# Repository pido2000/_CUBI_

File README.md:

### Description

Simple open source bluetooth controlled wheeled robot. Mechanical design, electronics and software designs available on this repo.
Remy F. used @Gregwar's Holo as a starting point.

The initial design is a cube like robot :

https://www.youtube.com/watch?v=2ZDV0_4vD0g

https://www.youtube.com/watch?v=TOusHRbKWQg

A second design was also made to play around cart-poling:

https://www.youtube.com/watch?v=Ubej95gH9Gs

TODO:

- Add Julien's O. designs and events

- Add Julien's A. and Jérémy's designs and event (cap science)

### Simulation
Some simulation stuff (simple kinematic control, inverted pendulum tests) is available in Python here :
https://bitbucket.org/RemiFabre/cubi/src/master/simulation/

0) Installation
You'll need Python (any version should work) and pygame
```
pip install pygame
```

1) Simple control of a wheeled robot (click around)
```
python main.py
```
https://www.youtube.com/watch?v=O8ZoUAvGYmE

2) Inverted pendulum (cart-pole) simulation
```
python cart_pole.py
```
https://www.youtube.com/watch?v=xhEcLnnj7fg

### How to make it work
You'll have to install the arm cross-compilation tools. On debian-like distributions,
you can get it with:

```
    sudo aptitude install build-essential git-core dfu-util openocd python \
        python-serial binutils-arm-none-eabi gcc-arm-none-eabi libstdc++-arm-none-eabi-newlib
```
If you're running an Ubuntu 14.04 or older, you might need to install the libstdc++-arm-none-eabi-newlib packet by hand. Download link :
http://ftp.de.debian.org/debian/pool/main/libs/libstdc++-arm-none-eabi/libstdc++-arm-none-eabi-newlib_4.8.3-9+4_all.deb

Command (if a conflict rises, you can add --force-overwrite to the following line):
```
	sudo dpkg -i libstdc++-arm-none-eabi-newlib_4.8.3-9+4_all.deb
```
Go to the `firmware/src` directory and edit the `Makefile` to set the appropriate
`BOARD` variable, targetting your servo.

You can then run:

```
make
```

Use an USB cable to connect your pc with the robot's board

```
make install
```
### Bluetooth

First you need to set the name and the pasword using a cable.

```
cu -l /dev/ttyACM0
btconf <name> <pswrd>
```

Then, you can control the robot without the need of a cable. The most straight-forward way is to download the "Metabot" app from Google Play. Once on the app you can scan for devices, find your robot and pair it with your phone.

If you want to pair your PC with your robot, one method is as follows (Ubuntu).

Uninstall modemmanager (not needed but causes some issues)

```
    sudo apt-get purge modemmanager
```

Scan for bluetooth devices and save the adress (e.g. 98:D3:37:90:ED:D6) of your robot. For example, we use blueman-manager :

```
    sudo apt-get install blueman
    sudo blueman-manager
```

Assign a serial port to the connection. You can do that on the graphical interface of blueman-manager but doing it directly with rfcomm seems more robust :

```
    sudo rfcomm bind /dev/rfcomm0 98:D3:37:90:ED:D6
```

Now you can access the remote terminal on the robot with :

```
    cu -l /dev/rfcomm0
```

You might have permission access issues. Make sure you're in the dialout group or go bonkers :

```
    sudo chmod 777 /dev/rfcomm0 && cu -l /dev/rfcomm0
```

### Electronics

A board was made with all integrated components in order to drop fabrication cost. 

Top

Bottom

### Mecanics

Cubi's design is simple. It consist of a squared box. The majority was made in MDF.

Visual from Onshape

The design is transposed in the following svg file.

We also enjoyed the look of PMMA.

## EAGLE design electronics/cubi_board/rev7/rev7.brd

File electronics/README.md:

### cubi_board

Recent schematics and pcbs which integrates all the components on a standalone board in order to reduce manufacturing costs.
The board contains a µC (STM32F103CBT6), a hc-05 Bluetooth module, some voltage regulators... However, the GY-85 imu module is not integrated directly on the board.

All revisions used Eagle EDA except the last revision (rev. 8) designed on EasyEDA.

### maple-mini_board

Old schematics and pcbs using Maple Mini boards, mostly developed on Eagle EDA.

### remake_board

Recent tests made on CUBI electronic boards, developed on KiCad EDA.

The goal was to separate the motor driver and the 9V to 5V voltage regulator (the supply part) from the rest of components.
We wanted to add magnetic connectors (Pogo conn) to have a Plug And Play device.

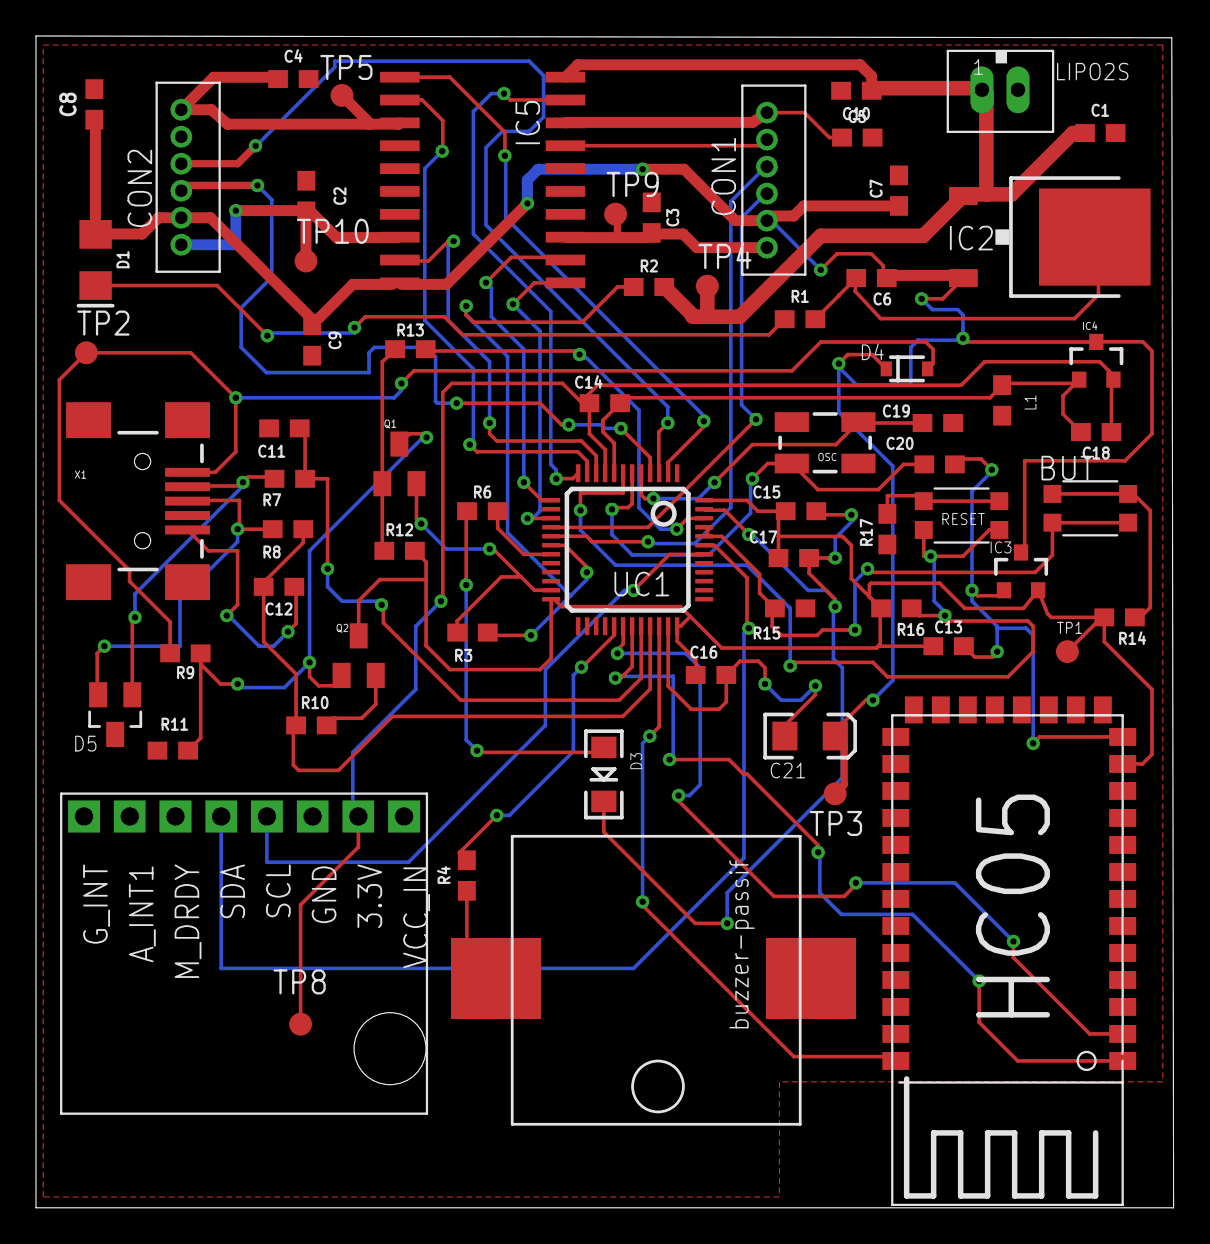
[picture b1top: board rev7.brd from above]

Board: 2 copper layers, 63.2 x 65.1 mm, 67 parts (0 on the bottom side), 47 nets.

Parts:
BUT: KMR211GLFS; PUSHBUTTON-KMR241GLFS
C1, C6: 0.1uF; 0603
C2, C3, C4, C5, C7, C8, C9, C10: 22nF; 0603
C11, C12: 47pF; 0603
C13, C18: 10uF; 0603
C14, C15, C16, C17: 1uF; 0603
C19, C20: 18pF; 0603
C21: 100uF; EIA3216
CON1, CON2: B6B-ZR
D1: FKIT-LED-1206
D3: Blue; LED-1206
D4: SOD-323
D5: PESD1CAN; SOT23
IC2: MC78M05ABDT; DPACK_3
IC3, IC4: MCP1703T-3302E/CB; SOT23
IC5: L293DD; SO20
L1: ferrite bead; 0603
LIPO2S: JST-PH_2-PIN_HEADER; JST_B2B-PH_HEADER
OSC: 8MHz; CRYSTAL-SMD-5X3
Q1, Q2: NPN-BJT; SOT23
R1: 133; 0603
R2: 60k; 0603
R3: 30k; 0603
R4: 100; 0603
R6, R13, R14, R17: 1k; 0603
R7, R8: 22; 0603
R9, R15, R16: 10k; 0603
R10: 1.5k; 0603
R11: 36k; 0603
R12: 47k; 0603
RESET: KMR211GLFS; PUSHBUTTON-KMR241GLFS
TP1, TP2, TP3, TP4, TP5, TP8, TP9, TP10: PTR1B1,27; B1,27
U$1: BUZZER-PASSIF
U$4: HC05; HC-05
U$6: GY-85
UC1: STM32F103CBT6; LQFP48
X1: USB-MINIB

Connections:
1A: IC5.2, UC1.11
2A: IC5.9, UC1.10
3/AIN: R2.1, R3.1, UC1.18
3A: IC5.12, UC1.13
4A: IC5.19, UC1.12
5V: C6.1, C7.1, C8.1, C9.1, C21.A, CON1.5, CON2.5, D1.A, D4.1, IC2.3, IC3.3, IC4.3, IC5.10, TP3.TP
9V: C1.1, C10.1, IC2.1, IC5.20, LIPO2S.P1, R2.2, TP4.TP
23_USBDP: C12.1, R8.1, R10.1, UC1.33
24_USBDM: C11.1, R7.1, UC1.32
27/PWM: R4.2, UC1.29
32: BUT.P$2, BUT.P$4, R15.2, UC1.44, UC1.45
33: R6.2, UC1.19
+5V/2: D4.2, R9.2, TP2.TP, X1.VBUS
AV+: C14.1, C18.1, IC4.2, TP8.TP, U$6.3.3, UC1.9
AV-: C14.2, C18.2, IC4.1, L1.1, UC1.8
DGND: C1.2, C2.1, C3.1, C4.2, C5.2, C7.2, C8.2, C9.2, C10.2, C11.2, C12.2, C13.2, C15.2, C16.2, C17.2, C19.2, C20.2, C21.C, CON1.2, CON2.2, D3.C, D5.3, IC3.1, IC5.4, IC5.5, IC5.6, IC5.7, IC5.14, IC5.15, IC5.16, IC5.17, L1.2, LIPO2S.P2, Q1.2, R3.2, R11.1, R15.1, R17.1, U$1.P$1, U$4.GND, U$6.GND, UC1.23, UC1.35, UC1.47, X1.GND
DISC: R13.2, UC1.46
EN: U$4.KEY, UC1.34
GNDA: C6.2, IC2.4, R1.2
MM4: CON2.3, UC1.3
MM5: CON2.4, UC1.4
MM6: CON1.4, UC1.16
MM7: CON1.3, UC1.17
MM28: IC5.1, UC1.2
MM29: IC5.11, UC1.15
unnamed: D1.C, R1.1
unnamed: R4.1, U$1.P$2
unnamed: BUT.P$1, BUT.P$3, R14.1
unnamed: R17.2, RESET.P$1, RESET.P$3
unnamed: D3.A, R6.1
unnamed: Q2.2, R10.2
unnamed: D5.1, R7.2, X1.D-
unnamed: D5.2, R8.2, X1.D+
unnamed: Q1.3, Q2.1, R9.1, R11.2
unnamed: Q1.1, R12.1, R13.1
OSC_IN: C19.1, OSC.3, UC1.5
OSC_OUT: C20.1, OSC.1, UC1.6
OUT1: C4.1, CON2.1, IC5.3, TP5.TP
OUT2: C2.2, CON2.6, IC5.8, TP10.TP
OUT3: C3.2, CON1.6, IC5.13, TP9.TP
OUT4: C5.1, CON1.1, IC5.18
RESET: R16.1, RESET.P$2, RESET.P$4, UC1.7
RX: U$4.RX, UC1.30
SCL: U$6.SCL, UC1.42
SDA: U$6.SDA, UC1.43
TX: U$4.TX, UC1.31
VCC: C13.1, C15.1, C16.1, C17.1, IC3.2, Q2.3, R12.2, R14.2, R16.2, TP1.TP, U$4.3.3, UC1.24, UC1.36, UC1.48

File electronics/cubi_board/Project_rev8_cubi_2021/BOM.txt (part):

Partlist exported from C:/Users/elkat/Documents/EAGLE/projects/electronics/rev7/rev7.sch at 24/09/2019 17:15

Part   Value               Device                     Package               Description                               FARNELL      MF MPN OC_FARNELL PROD_ID   TP_SIGNAL_NAME VALUE
BUT    KMR211GLFS          BUTTON-KMR241GLFS          PUSHBUTTON-KMR241GLFS                                                                                                        
C1     0.1uF               0.1UF-0603-25V-(+80/-20%)  0603                  0.1µF ceramic capacitors                                                 CAP-00810                0.1uF
C2     22nF                22NF/22,000PF-0603-50V-10% 0603                  0.022uF/22nF/22,000pF ceramic capacitors                                 CAP-07885                22nF 
C3     22nF                22NF/22,000PF-0603-50V-10% 0603                  0.022uF/22nF/22,000pF ceramic capacitors                                 CAP-07885                22nF 
C4     22nF                22NF/22,000PF-0603-50V-10% 0603                  0.022uF/22nF/22,000pF ceramic capacitors                                 CAP-07885                22nF 
C5     22nF                22NF/22,000PF-0603-50V-10% 0603                  0.022uF/22nF/22,000pF ceramic capacitors                                 CAP-07885                22nF 
C6     0.1uF               0.1UF-0603-25V-(+80/-20%)  0603                  0.1µF ceramic capacitors                                                 CAP-00810                0.1uF
C7     22nF                22NF/22,000PF-0603-50V-10% 0603                  0.022uF/22nF/22,000pF ceramic capacitors                                 CAP-07885                22nF 
C8     22nF                22NF/22,000PF-0603-50V-10% 0603                  0.022uF/22nF/22,000pF ceramic capacitors                                 CAP-07885                22nF 
C9     22nF                22NF/22,000PF-0603-50V-10% 0603                  0.022uF/22nF/22,000pF ceramic capacitors                                 CAP-07885                22nF 
C10    22nF                22NF/22,000PF-0603-50V-10% 0603                  0.022uF/22nF/22,000pF ceramic capacitors                                 CAP-07885                22nF 
C11    47pF                0.1UF-0603-25V-(+80/-20%)  0603                  0.1µF ceramic capacitors                                                 CAP-00810                0.1uF
C12    47pF                0.1UF-0603-25V-(+80/-20%)  0603                  0.1µF ceramic capacitors                                                 CAP-00810                0.1uF
C13    10uF                0.1UF-0603-25V-(+80/-20%)  0603                  0.1µF ceramic capacitors                                                 CAP-00810                0.1uF
C14    1uF                 0.1UF-0603-25V-(+80/-20%)  0603                  0.1µF ceramic capacitors                                                 CAP-00810                0.1uF
C15    1uF                 0.1UF-0603-25V-(+80/-20%)  0603                  0.1µF ceramic capacitors                                                 CAP-00810                0.1uF
C16    1uF                 0.1UF-0603-25V-(+80/-20%)  0603                  0.1µF ceramic capacitors                                                 CAP-00810                0.1uF
C17    1uF                 0.1UF-0603-25V-(+80/-20%)  0603                  0.1µF ceramic capacitors                                                 CAP-00810                0.1uF
C18    10uF                0.1UF-0603-25V-(+80/-20%)  0603                  0.1µF ceramic capacitors                                                 CAP-00810                0.1uF
C19    18pF                0.1UF-0603-25V-(+80/-20%)  0603                  0.1µF ceramic capacitors                                                 CAP-00810                0.1uF
C20    18pF                0.1UF-0603-25V-(+80/-20%)  0603                  0.1µF ceramic capacitors                                                 CAP-00810                0.1uF
C21    100uF               CAP_POL1206                EIA3216               Capacitor Polarized                                                                                    
CON1   B6B-ZR              B6B-ZR                     B6B-ZR                JST-ZH Connector                                                                                       
CON2   B6B-ZR              B6B-ZR                     B6B-ZR                JST-ZH Connector                                                                                       
D1                         LED-FKIT-1206              FKIT-LED-1206         LED (Generic)                                                                                          
D3     Blue                LED1206                    LED-1206              LEDs                                                                                                   
D4                         DIODESOD                   SOD-323               Diode                                                                                                  
D5     PESD1CAN            PESD1CAN                   SOT23                 CAN bus ESD protection diode                                                                           
IC2    MC78M05ABDT         MC78M05ABDT                DPACK_3               500 mA Positive Voltage Regulators                                                                     
IC3    MCP1703T-3302E/CB   MCP1700T                   SOT23                                                                                                                        
IC4    MCP1703T-3302E/CB   MCP1700T                   SOT23                                                                                                                        
IC5    L293DD              L293DD                     SO20                  PUSH-PULL FOUR CHANNEL DRIVER WITH DIODES                     unknown                                  
L1     ferrite bead        INDUCTOR0603               0603                  Inductors                                                                                              
LIPO2S JST-PH_2-PIN_HEADER JST-PH_2-PIN_HEADER        JST_B2B-PH_HEADER     2-pin JST PH Shrouded Header, top entry                                                                
OSC    8MHz                CRYSTAL5X3                 CRYSTAL-SMD-5X3       Crystals                                                                                               
Q1     NPN-BJT             TRANSISTOR_NPNSOT23        SOT23                 Transistor NPN                                                                                         
Q2     NPN-BJT             TRANSISTOR_NPNSOT23        SOT23                 Transistor NPN                                                                                         
R1     133                 0.27OHM-0603-1/10W-1%      0603                  0.27Ω resistor                                                           RES-08787                0.27 
R2     60k                 0.27OHM-0603-1/10W-1%      0603                  0.27Ω resistor                                                           RES-08787                0.27 
R3     30k                 0.27OHM-0603-1/10W-1%      0603                  0.27Ω resistor                                                           RES-08787                0.27 
R4     100                 0.27OHM-0603-1/10W-1%      0603                  0.27Ω resistor                                                           RES-08787                0.27 
R6     1k                  0.27OHM-0603-1/10W-1%      0603                  0.27Ω resistor                                                           RES-08787                0.27 
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
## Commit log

2021-06-30 Initial files
2021-06-30 Adding Maple library
2021-06-30 Adding current CUBI_BOX layout
2021-06-30 New organisatin of docs
2021-06-30 Move electronics
2021-06-30 Update electronics & mechanics
2021-07-01 README for elec
2021-07-01 Cubi's box .svg
2021-07-01 change src
2021-07-06 uploading pictures
2021-07-06 pictures uploaded
2021-07-06 uploading pictures [meca][elec]
2021-07-06 Updating README (pictures&bluetooth related info)
2021-07-06 Adding README for driveur_moteur project
2021-07-09 Correction README du driver moteur, partie elec
2021-07-09 Update README, electronics part
2021-08-02 remove unwanted filed

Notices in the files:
parts and their libraries:
SparkFun-Capacitors: Licensing: Creative Commons ShareAlike 4.0 International - https://creativecommons.org/licenses/by-sa/4.0
